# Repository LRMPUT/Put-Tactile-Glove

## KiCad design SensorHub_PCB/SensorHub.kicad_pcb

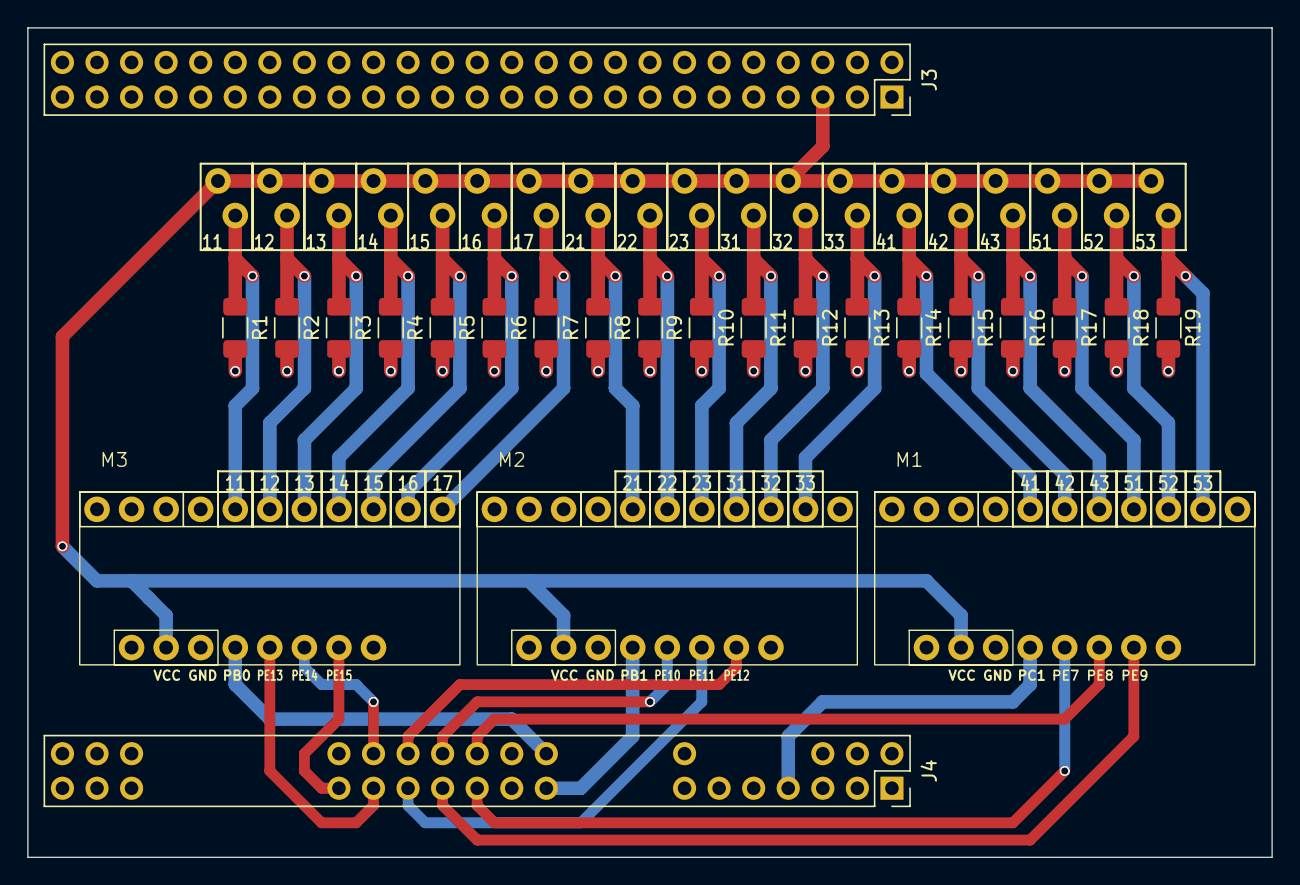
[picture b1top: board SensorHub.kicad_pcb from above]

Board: 2 copper layers, 91.4 x 61.0 mm, 26 parts (0 on the bottom side), 33 nets.

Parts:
J1, J2: Pin_Connector_01x19; czujniki
J3: Conn_2Rows-51Pins_LEFT; PinSocket_2x25_P2.54mm_Vertical
J4: Conn_2Rows-51Pins_RIGHT; lewastrona
M1, M2, M3: Multiplekser; pod_multi_11
R1, R2, R3, R4, R5, R6, R7: 2,2k; R_1206_3216Metric_Pad1.30x1.75mm_HandSolder
R8, R9, R10, R11, R12, R13, R14, R15, R16, R17, R18, R19: 4,7k; R_1206_3216Metric_Pad1.30x1.75mm_HandSolder

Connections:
11: J2.1, M3.5 (Y1), R1.1
12: J2.2, M3.6 (Y2), R2.1
13: J2.3, M3.7 (Y3), R3.1
14: J2.4, M3.8 (Y4), R4.1
15: J2.5, M3.9 (Y5), R5.1
16: J2.6, M3.10 (Y6), R6.1
17: J2.7, M3.11 (Y7), R7.1
21: J2.8, M2.5 (Y1), R8.1
22: J2.9, M2.6 (Y2), R9.1
23: J2.10, M2.7 (Y3), R10.1
31: J2.11, M2.8 (Y4), R11.1
32: J2.12, M2.9 (Y5), R12.1
33: J2.13, M2.10 (Y6), R13.1
41: J2.14, M1.5 (Y1), R14.1
42: J2.15, M1.6 (Y2), R15.1
43: J2.16, M1.7 (Y3), R16.1
51: J2.17, M1.8 (Y4), R17.1
52: J2.18, M1.9 (Y5), R18.1
53: J2.19, M1.10 (Y6), R19.1
GND: J3.1, J3.2, J4.2, M1.14 (GND), M2.14 (GND), M3.14 (GND), R1.2, R2.2, R3.2, R4.2, R5.2, R6.2, R7.2, R8.2, R9.2, R10.2, R11.2, R12.2, R13.2, R14.2, R15.2, R16.2, R17.2, R18.2, R19.2
PB0: J4.22, M3.15 (Z)
PB1: J4.21, M2.15 (Z)
PC1: J4.7, M1.15 (Z)
PE7: J4.25, M1.16 (S0)
PE8: J4.26, M1.17 (S1)
PE9: J4.27, M1.18 (S2)
PE10: J4.28, M2.16 (S0)
PE11: J4.29, M2.17 (S1)
PE12: J4.30, M2.18 (S2)
PE13: J4.31, M3.16 (S0)
PE14: J4.32, M3.17 (S1)
PE15: J4.33, M3.18 (S2)
VCC: J1.1, J1.2, J1.3, J1.4, J1.5, J1.6, J1.7, J1.8, J1.9, J1.10, J1.11, J1.12, J1.13, J1.14, J1.15, J1.16, J1.17, J1.18, J1.19, J3.5, M1.13 (VCC), M2.13 (VCC), M3.13 (VCC)

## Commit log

2024-01-26 linearization model
2024-01-26 ROS2
2024-01-26 config
2024-01-27 add microROS-stm32 project
2024-01-27 Add electronics housing fusion and stl files
2024-02-14 correlation.py error_chart.py
2024-02-14 add name
2024-02-14 sensor for silicone and overlays
